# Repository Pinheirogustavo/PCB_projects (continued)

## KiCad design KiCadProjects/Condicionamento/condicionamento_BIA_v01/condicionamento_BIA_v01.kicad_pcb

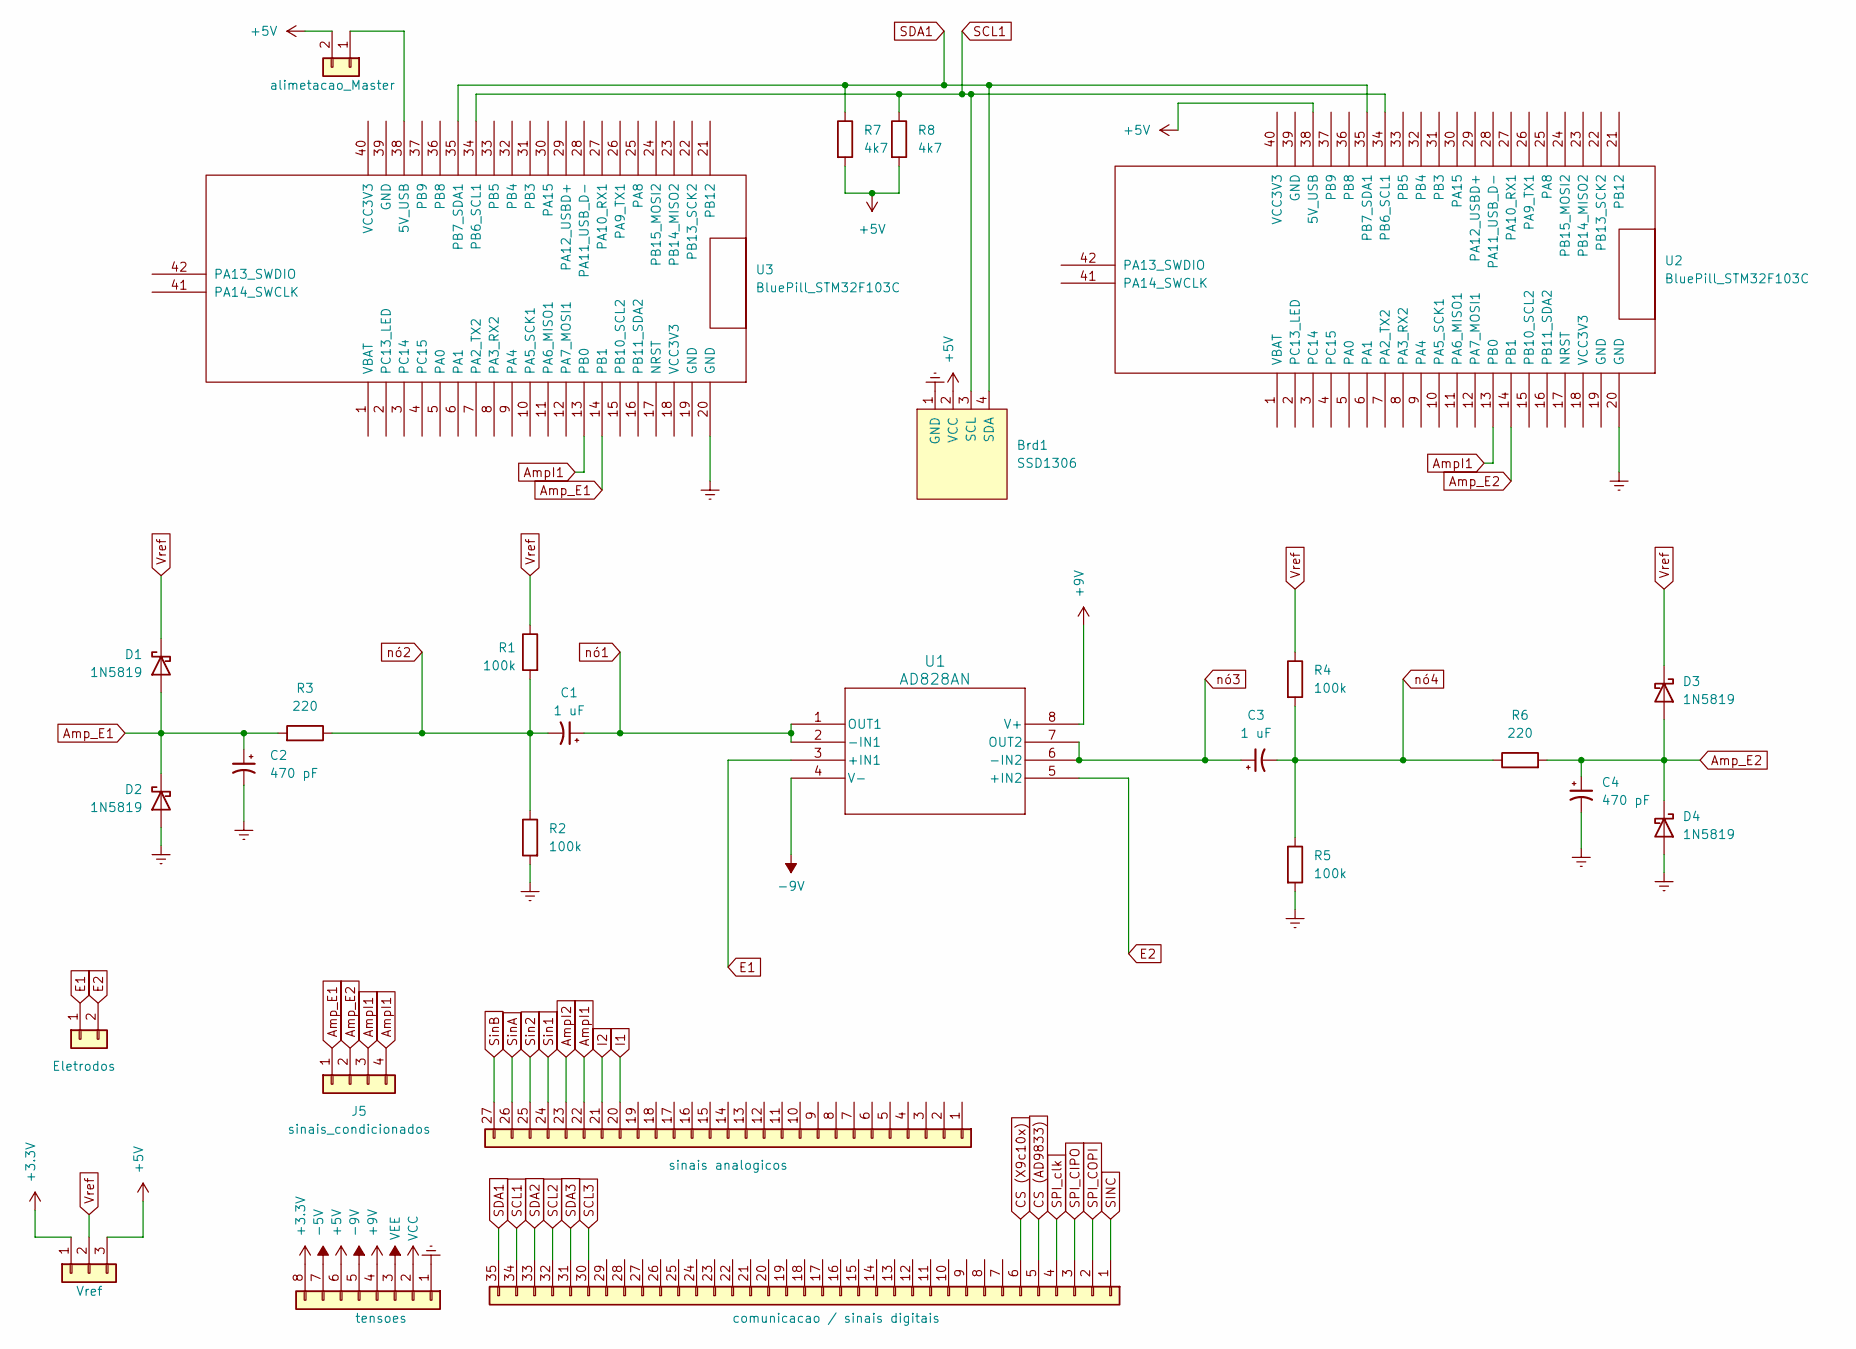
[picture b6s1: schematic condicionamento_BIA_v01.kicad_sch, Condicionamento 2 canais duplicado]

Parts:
Brd1: SSD1306; 128x64OLED
C1, C3: 1 uF; CP_Radial_D5.0mm_P2.50mm
C2, C4: 470 pF; CP_Radial_D5.0mm_P2.50mm
D1, D2, D3, D4: 1N5819; D_DO-41_SOD81_P10.16mm_Horizontal
J1: Vref; PinHeader_1x03_P2.54mm_Vertical
J2: tensoes; PinHeader_1x08_P2.54mm_Vertical
J3: sinais analogicos; PinHeader_1x27_P2.54mm_Vertical
J4: comunicacao / sinais digitais; PinHeader_1x35_P2.54mm_Vertical
J5: sinais_condicionados; PinHeader_1x04_P2.54mm_Horizontal
J6: alimetacao_Master; PinHeader_1x02_P2.54mm_Vertical
J7: Eletrodos; PinHeader_1x02_P2.54mm_Horizontal
R1, R2, R4, R5: 100k; R_Axial_DIN0207_L6.3mm_D2.5mm_P7.62mm_Horizontal
R3, R6: 220; R_Axial_DIN0207_L6.3mm_D2.5mm_P7.62mm_Horizontal
R7, R8: 4k7; R_Axial_DIN0207_L6.3mm_D2.5mm_P7.62mm_Horizontal
U1: AD828AN; N_8_ADI
U2, U3: BluePill_STM32F103C

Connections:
+3.3V: J1.1, J2.8
+5V: Brd1.2 (VCC), J1.3, J2.6, J6.2, R7.2, R8.2, U2.38 (5V_USB); also elsewhere on the board
+9V: J2.4, U1.8 (V+)
-5V: J2.7
-9V: J2.5, U1.4 (V-)
AmpI1: J3.22, J5.3, J5.4, U2.13 (PB0), U3.13 (PB0)
AmpI2: J3.23
Amp_E1: C2.1, D1.2 (A), D2.1 (K), J5.1, R3.2, U3.14 (PB1)
Amp_E2: C4.1, D3.2 (A), D4.1 (K), J5.2, R6.2, U2.14 (PB1)
CS (AD9833): J4.5
CS (X9c10x): J4.6
E1: J7.1, U1.3 (+IN1)
E2: J7.2, U1.5 (+IN2)
Earth: Brd1.1 (GND), C2.2, C4.2, D2.2 (A), D4.2 (A), J2.1, R2.2, R5.2, U2.20 (GND), U3.20 (GND)
I1: J3.20
I2: J3.21
unnamed: J6.1, U3.38 (5V_USB)
SCL1: Brd1.3 (SCL), J4.34, R8.1, U2.34 (PB6_SCL1), U3.34 (PB6_SCL1); also elsewhere on the board
SCL2: J4.32
SCL3: J4.30
SDA1: Brd1.4 (SDA), J4.35, R7.1, U2.35 (PB7_SDA1), U3.35 (PB7_SDA1); also elsewhere on the board
SDA2: J4.33
SDA3: J4.31
SINC: J4.1
SPI_CIPO: J4.3
SPI_COPI: J4.2
SPI_clk: J4.4
Sin1: J3.24
Sin2: J3.25
SinA: J3.26
SinB: J3.27
VCC: J2.2
VEE: J2.3
Vref: D1.1 (K), D3.1 (K), J1.2, R1.1, R4.1
nó1: C1.1, U1.1 (OUT1), U1.2 (-IN1)
nó2: C1.2, R1.2, R2.1, R3.1
nó3: C3.1, U1.6 (-IN2), U1.7 (OUT2)
nó4: C3.2, R4.2, R5.1, R6.1

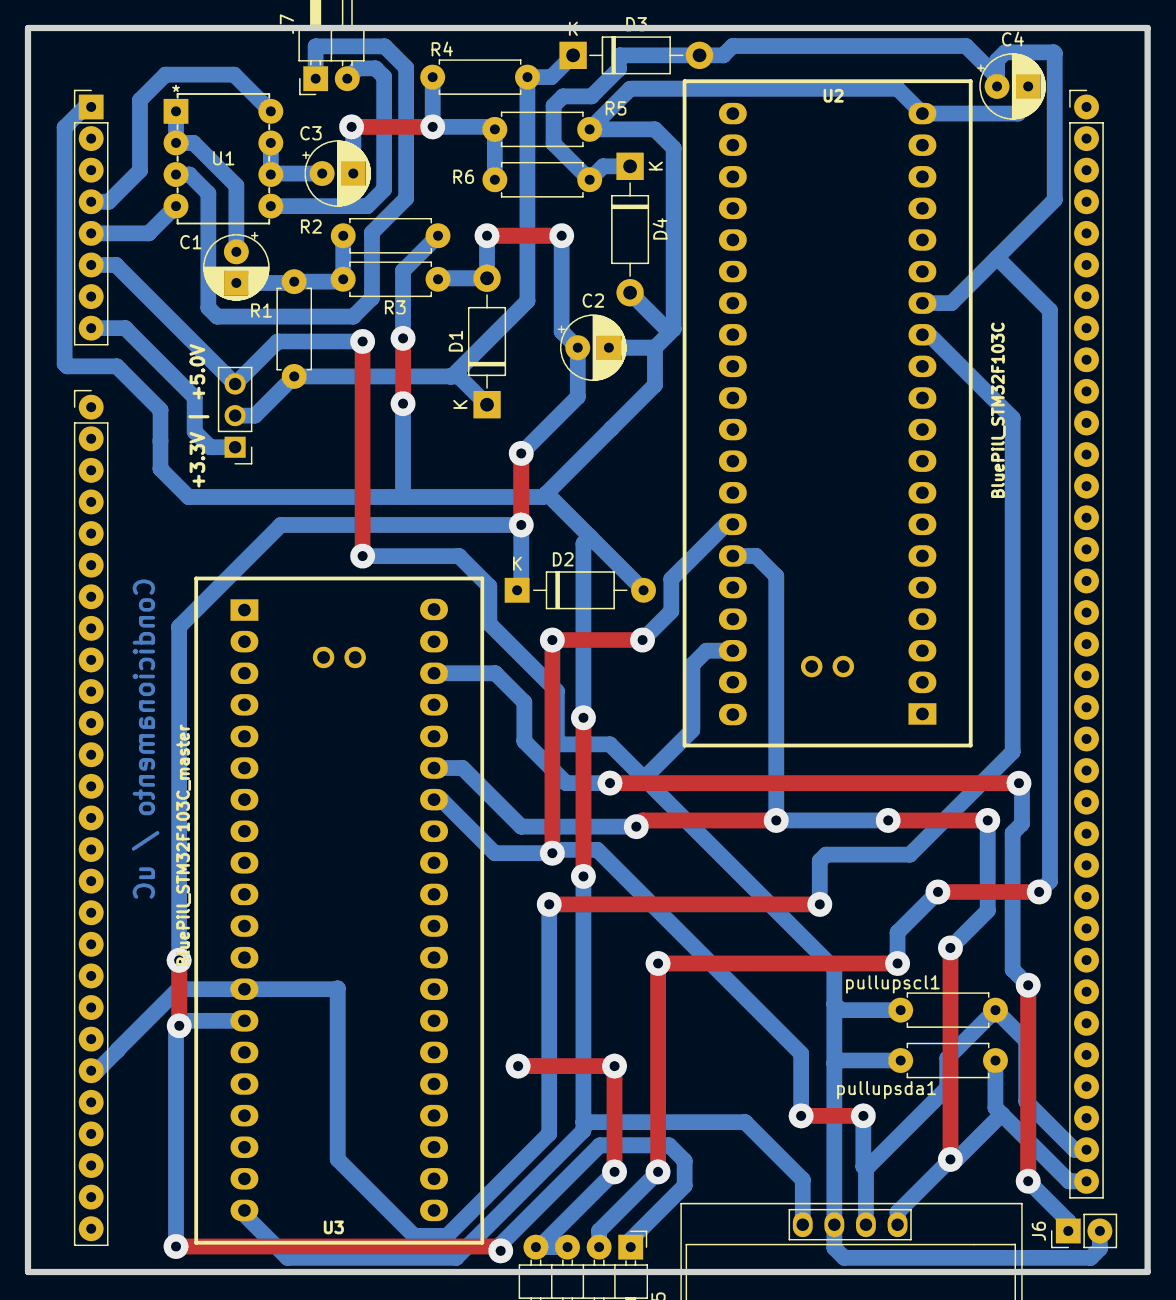
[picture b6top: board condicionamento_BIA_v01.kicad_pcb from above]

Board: 2 copper layers, 90.0 x 100.0 mm, 27 parts (0 on the bottom side), 18 nets.

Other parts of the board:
pullupscl1: 4k7; R_Axial_DIN0207_L6.3mm_D2.5mm_P7.62mm_Horizontal
pullupsda1: 4k7; R_Axial_DIN0207_L6.3mm_D2.5mm_P7.62mm_Horizontal

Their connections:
+5V: pullupscl1.2, pullupsda1.2; also elsewhere on the board
SCL1: pullupscl1.1; also elsewhere on the board
SDA1: pullupsda1.1; also elsewhere on the board
